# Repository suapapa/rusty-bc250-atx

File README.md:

# Rusty BC250 ATX

- [In Action Video](https://www.youtube.com/watch?v=EkOmVfLqIu4)

ATX PSU soft-power adapter for the AMD BC250 mining board.
The BC250 lacks native ATX PS_ON circuitry; this firmware bridges that gap using a CH32V003 microcontroller.

## Features

| Function | Description |
|----------|-------------|
| PS_ON control | Drive ATX PS_ON via optocoupler — active LOW at ATX connector, active HIGH at MCU |
| HOST_ON sense | Detect BC250 running state via optocoupler (12 V → 3.3 V isolated) |
| Power button | Debounced momentary button with short-press / long-press detection |
| Force off | 4-second hold → hard-cut ATX PS_ON regardless of HOST_ON state |
| LED output | Power status indicator (15 mA limited; J1 bypass up to 250 mA) |

## Board Assembly

The prototype PCB shown below was manufactured using a 3D printer.
- [sch/](sch/rusty-bc250-atx/) — KiCad schematic and PCB design
- [pcb_3dprint/](pcb_3dprint/) — STL and OpenSCAD files for 3D-printed PCB prototyping

## Power State Machine

```
IDLE
 └─ short press ──────────→ assert PS_ON ──→ POWERING_ON

POWERING_ON
 ├─ HOST_ON low ──────────→ RUNNING
 └─ timeout 5 s ──────────→ de-assert PS_ON ──→ IDLE   (PSU failed to start)

RUNNING
 ├─ hold 3 s ─────────────→ LED fast-blink warning
 ├─ hold 4 s ─────────────→ force de-assert PS_ON ──→ IDLE
 └─ HOST_ON lost 500 ms ──→ de-assert PS_ON ──→ IDLE
```

## Hardware

- **MCU** — CH32V003F4U6 (RISC-V RV32EC, TSSOP-20)
- **Programmer** — WCH-LinkE via SWIO (PD1)
- See [PINMAP.md](PINMAP.md) for pin assignments
- See [CIRCUIT.md](CIRCUIT.md) for circuit diagrams
- See [BOM.md](BOM.md) for the full bill of materials

## Building

Rust nightly toolchain is required (`riscv32ec` target is not yet stable).
The correct toolchain is pinned via `rust-toolchain.toml`.

```bash
cargo build --release
```

## Flashing

Install [wlink](https://github.com/ch32-rs/wlink):

```bash
cargo install --git https://github.com/ch32-rs/wlink
```

Connect a WCH-LinkE probe to the board (SWIO → PD1, GND, 3.3 V), then:

```bash
cargo run --release
```

Serial debug output (SDI print) is enabled automatically and streamed by `wlink`.

## License

Licensed under the [MIT License](LICENSE-MIT).

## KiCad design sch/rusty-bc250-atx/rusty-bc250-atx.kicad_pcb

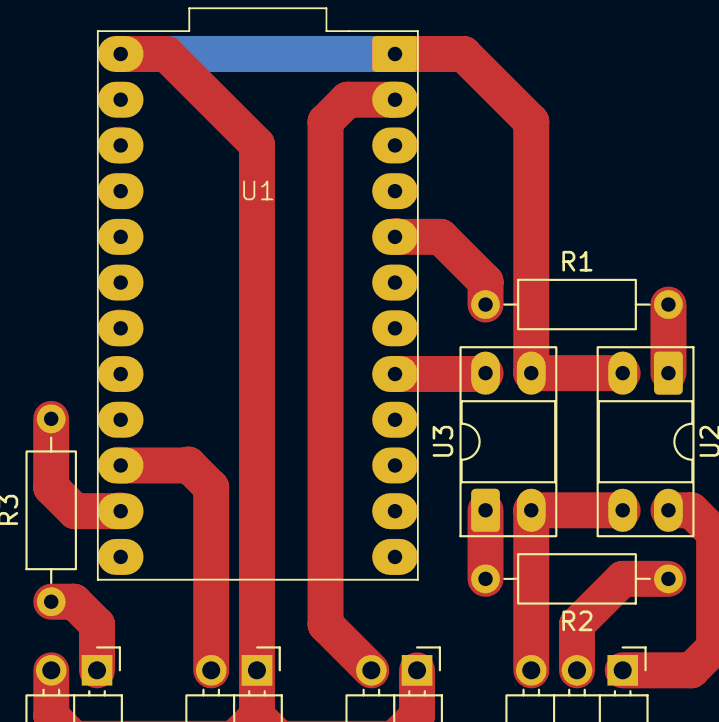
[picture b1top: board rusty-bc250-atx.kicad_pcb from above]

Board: 2 copper layers, 10 parts (0 on the bottom side), 12 nets.

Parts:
J1: PWR_LED; PinHeader_1x02_P2.54mm_Horizontal
J4: 5V_SB; PinHeader_1x02_P2.54mm_Horizontal
J5: PWR_SW; PinHeader_1x02_P2.54mm_Horizontal
J6: Conn_01x03_Pin; PinHeader_1x03_P2.54mm_Horizontal
R1, R2: 1k; R_Axial_DIN0207_L6.3mm_D2.5mm_P10.16mm_Horizontal
R3: 100; R_Axial_DIN0207_L6.3mm_D2.5mm_P10.16mm_Horizontal
U1: CH32V003_CoreBoard_2
U2, U3: Optocoupler_DC_PhotoNPN_AKEC; DIP-4_W7.62mm_Socket_LongPads

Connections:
5V: J4.2, U1.2 (VIN)
/ATX_PS_ON_N: J6.1, U2.4
/BC250_HOST_ON: J6.2, R2.1
ATX_GND: J6.3, U2.3, U3.2
GND: J1.2, J4.1, J5.1, U1.1 (GND), U1.24 (GND), U2.2, U3.3
unnamed: J1.1, R3.1
unnamed: J5.2, U1.15 (PD4)
unnamed: R1.2, U2.1
unnamed: R2.2, U3.1
unnamed: R3.2, U1.14 (PD5)
unnamed: U1.8 (PC0), U3.4
unnamed: R1.1, U1.5 (PC3)

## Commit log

2026-04-17 rename project: ch32-bc250-atx -> rusty-bc250-atx
2026-04-17 docs: add webp assets, add stl exports and update README
2026-04-20 docs: add video
